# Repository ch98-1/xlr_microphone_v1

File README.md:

# xlr_microphone_v1
48v phantom powered xlr condenser microphone with 10 capsules made to fit BM-800 mic body

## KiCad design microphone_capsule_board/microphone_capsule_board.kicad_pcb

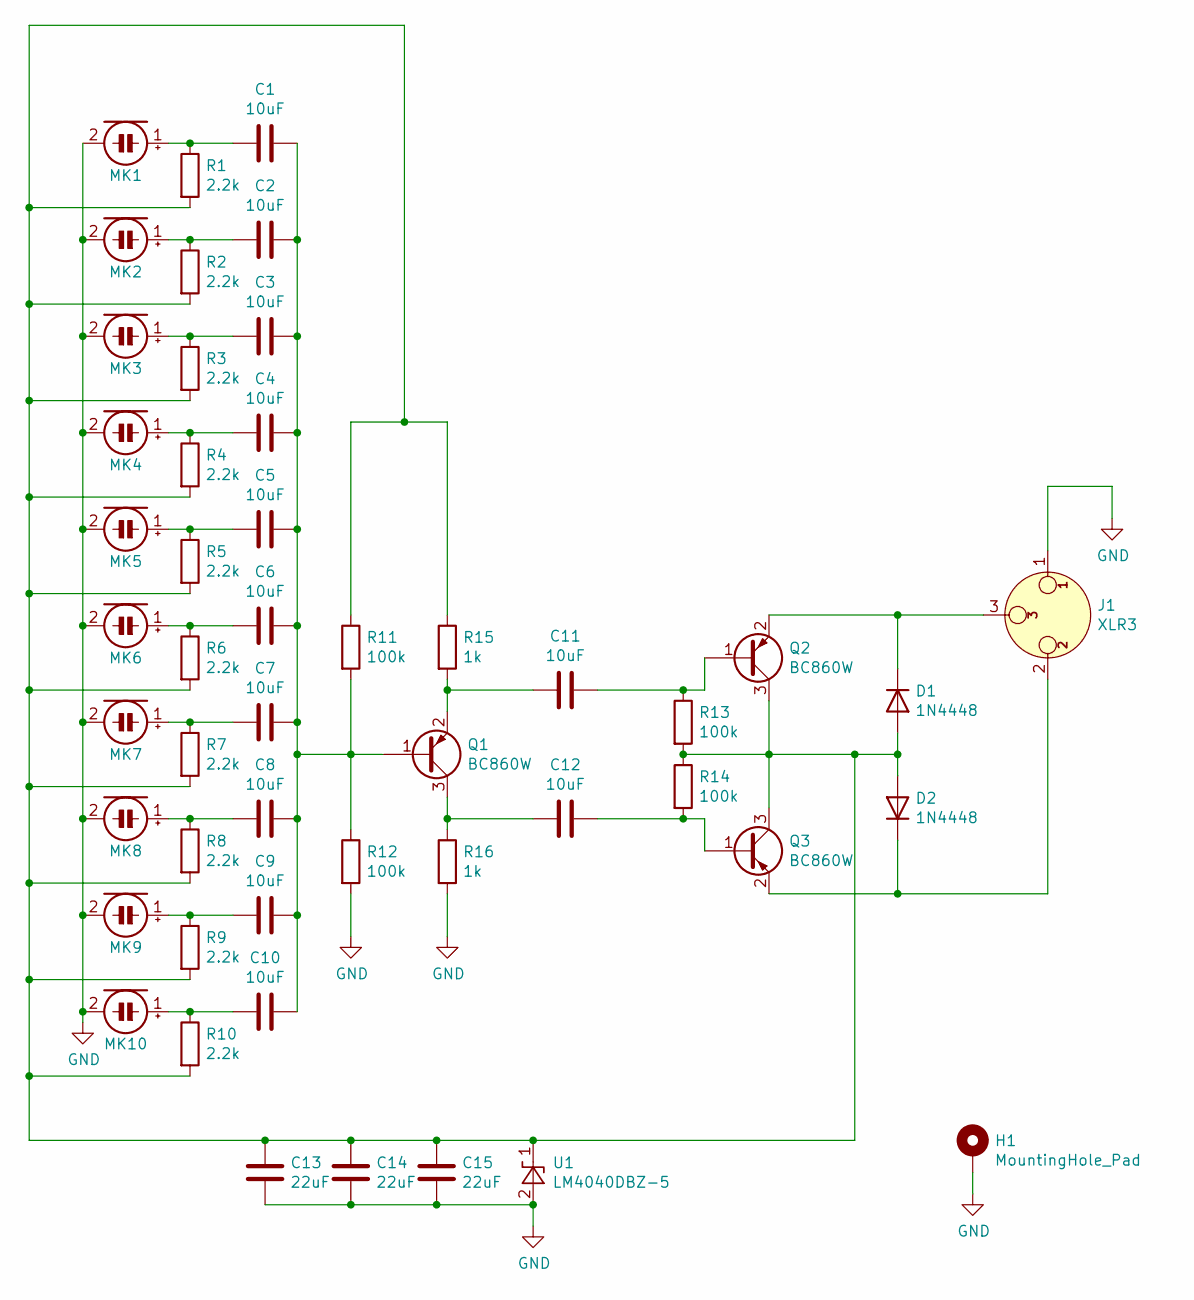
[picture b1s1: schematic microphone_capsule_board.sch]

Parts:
C1, C2, C3, C4, C5, C6, C7, C8, C9, C10, C11, C12: 10uF; C_1210_3225Metric
C13, C14, C15: 22uF; C_1210_3225Metric
D1, D2: 1N4448; D_SOD-123
H1: MountingHole_Pad; MountingHole_2.2mm_M2_Pad_Via
J1: XLR3; PinHeader_1x03_P2.54mm_Vertical
MK1, MK2, MK3, MK4, MK5, MK6, MK7, MK8, MK9, MK10: Electret_Condenser_Microphone; CUI_CMA-6542PF
Q1, Q2, Q3: BC860W; SOT-323_SC-70
R1, R2, R3, R4, R5, R6, R7, R8, R9, R10: 2.2k; R_0402_1005Metric
R11, R12, R13, R14: 100k; R_0805_2012Metric
R15, R16: 1k; R_0805_2012Metric
U1: LM4040DBZ-5; SOT-23

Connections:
GND: C13.2, C14.2, C15.2, H1.1, J1.1, MK1.2 (+), MK2.2 (+), MK3.2 (+), MK4.2 (+), MK5.2 (+), MK6.2 (+), MK7.2 (+), MK8.2 (+), MK9.2 (+), MK10.2 (+), R12.2, R16.2, U1.2 (A)
unnamed: C1.1, C2.1, C3.1, C4.1, C5.1, C6.1, C7.1, C8.1, C9.1, C10.1, Q1.1 (B), R11.2, R12.1
unnamed: C1.2, MK1.1 (-), R1.1
unnamed: C2.2, MK2.1 (-), R2.1
unnamed: C3.2, MK3.1 (-), R3.1
unnamed: C4.2, MK4.1 (-), R4.1
unnamed: C5.2, MK5.1 (-), R5.1
unnamed: C6.2, MK6.1 (-), R6.1
unnamed: C7.2, MK7.1 (-), R7.1
unnamed: C8.2, MK8.1 (-), R8.1
unnamed: C9.2, MK9.1 (-), R9.1
unnamed: C10.2, MK10.1 (-), R10.1
unnamed: C11.1, Q2.1 (B), R13.1
unnamed: C11.2, Q1.2 (E), R15.2
unnamed: C12.1, Q3.1 (B), R14.2
unnamed: C12.2, Q1.3 (C), R16.1
unnamed: C13.1, C14.1, C15.1, D1.2 (A), D2.2 (A), Q2.3 (C), Q3.3 (C), R1.2, R2.2, R3.2, R4.2, R5.2, R6.2, R7.2, R8.2, R9.2, R10.2, R11.1, R13.2, R14.1, R15.1, U1.1 (K)
unnamed: D1.1 (K), J1.3, Q2.2 (E)
unnamed: D2.1 (K), J1.2, Q3.2 (E)

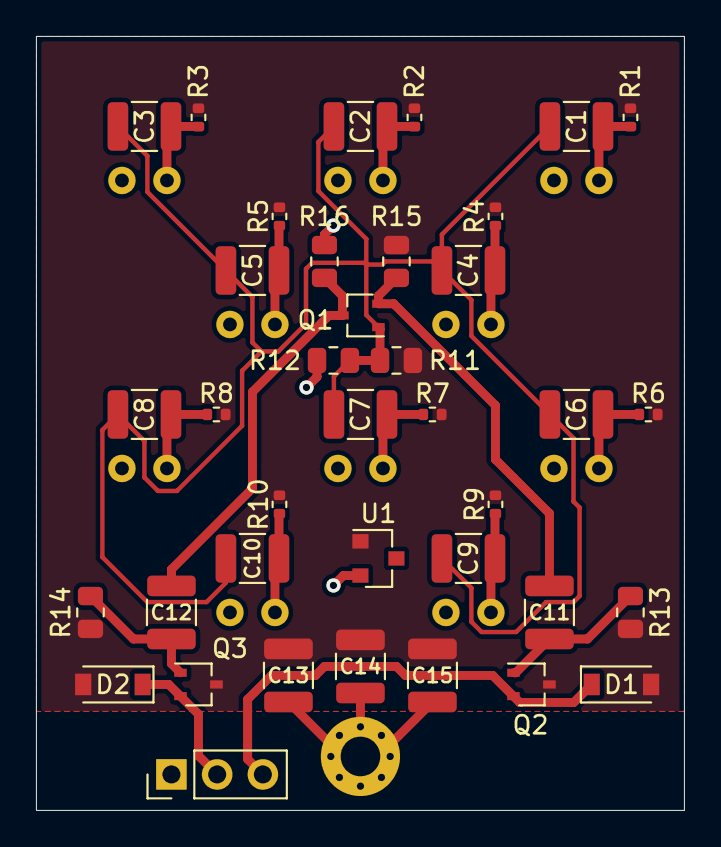
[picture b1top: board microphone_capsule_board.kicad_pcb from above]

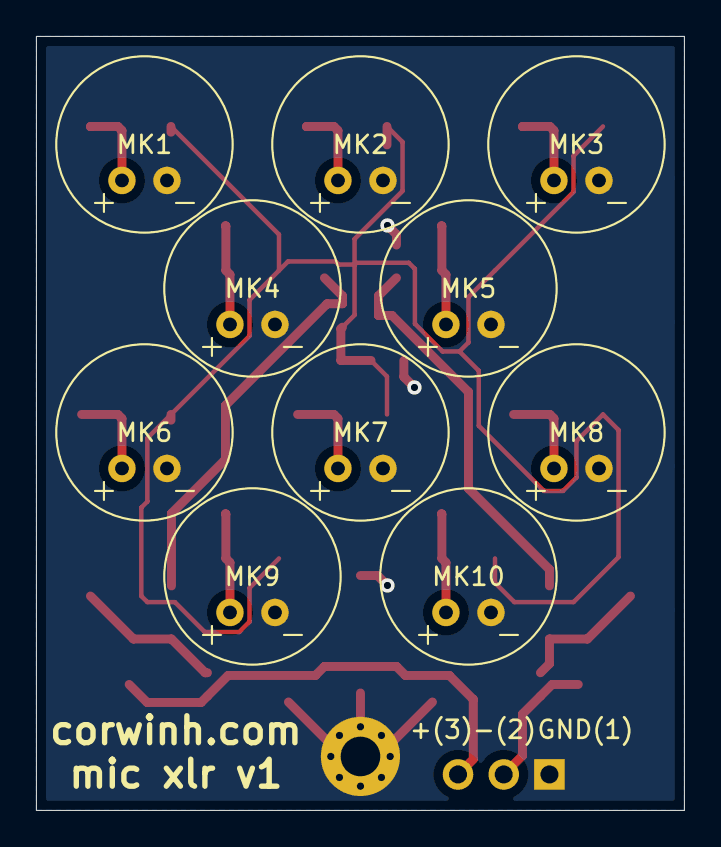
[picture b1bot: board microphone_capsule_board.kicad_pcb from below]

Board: 2 copper layers, 36.0 x 43.0 mm, 49 parts (10 on the bottom side), 19 nets.

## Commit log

2021-12-12 made v1 of the board
2022-01-20 Added License
